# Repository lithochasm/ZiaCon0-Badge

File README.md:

# ZiaCon0-Badge
Badge code and hardware schematics for the ZiaCon0 Badge

KiCad project and gerbers are located in the Hardware Folder

An Ardunio project is located in the software folder. Please note that
the .ino project is blank. It just pulls in the tinytouch libraries. In the 
tinytouch library folder there is a main.c file which contains the badge code.
I did not have time to pull the code out of there and make a proper ardunio project so
I just ran with what the library was already pointing to. 

# Resources

How to program an ATTiny13A with an arduino: https://www.hackster.io/taunoerik/programming-attiny13-with-arduino-uno-07beba

Low Power tips for an ATTiny13: https://homecircuits.eu/blog/low-power-picopower-attiny13a/

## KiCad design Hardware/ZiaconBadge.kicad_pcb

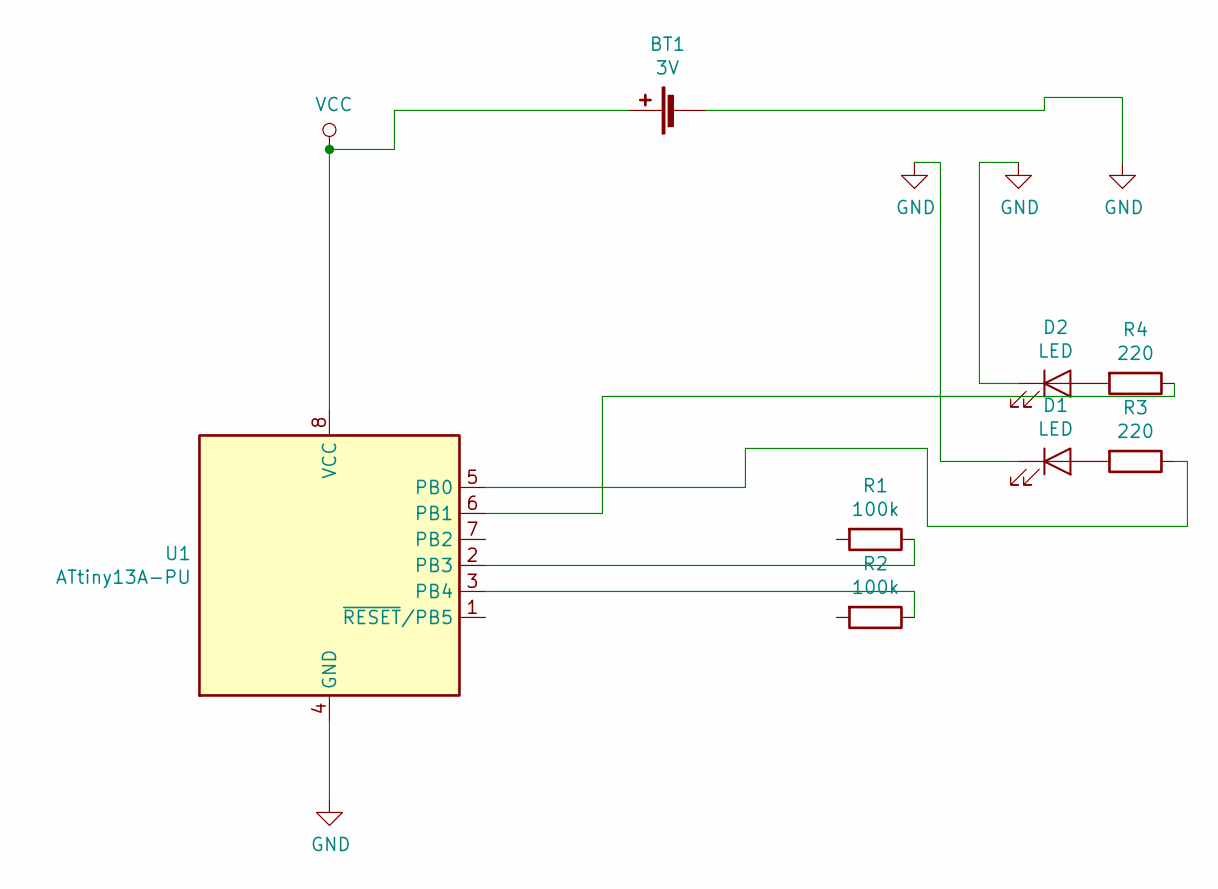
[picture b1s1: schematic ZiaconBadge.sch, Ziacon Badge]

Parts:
BT1: 3V; Battery_Holder_Coin_2032_BS-7
D1, D2: LED; LED_D3.0mm
R1, R2: 100k; R_Axial_DIN0207_L6.3mm_D2.5mm_P7.62mm_Horizontal
R3, R4: 220; R_Axial_DIN0207_L6.3mm_D2.5mm_P7.62mm_Horizontal
U1: ATtiny13A-PU; DIP-8_W7.62mm

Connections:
GND: BT1.2 (-), D1.1 (K), D2.1 (K), U1.4 (GND)
unnamed: D1.2 (A), R3.2
unnamed: D2.2 (A), R4.2
unnamed: R1.1, U1.2 (PB3)
unnamed: R2.1, U1.3 (PB4)
unnamed: R3.1, U1.5 (PB0)
unnamed: R4.1, U1.6 (PB1)
VCC: BT1.1 (+), U1.8 (VCC)

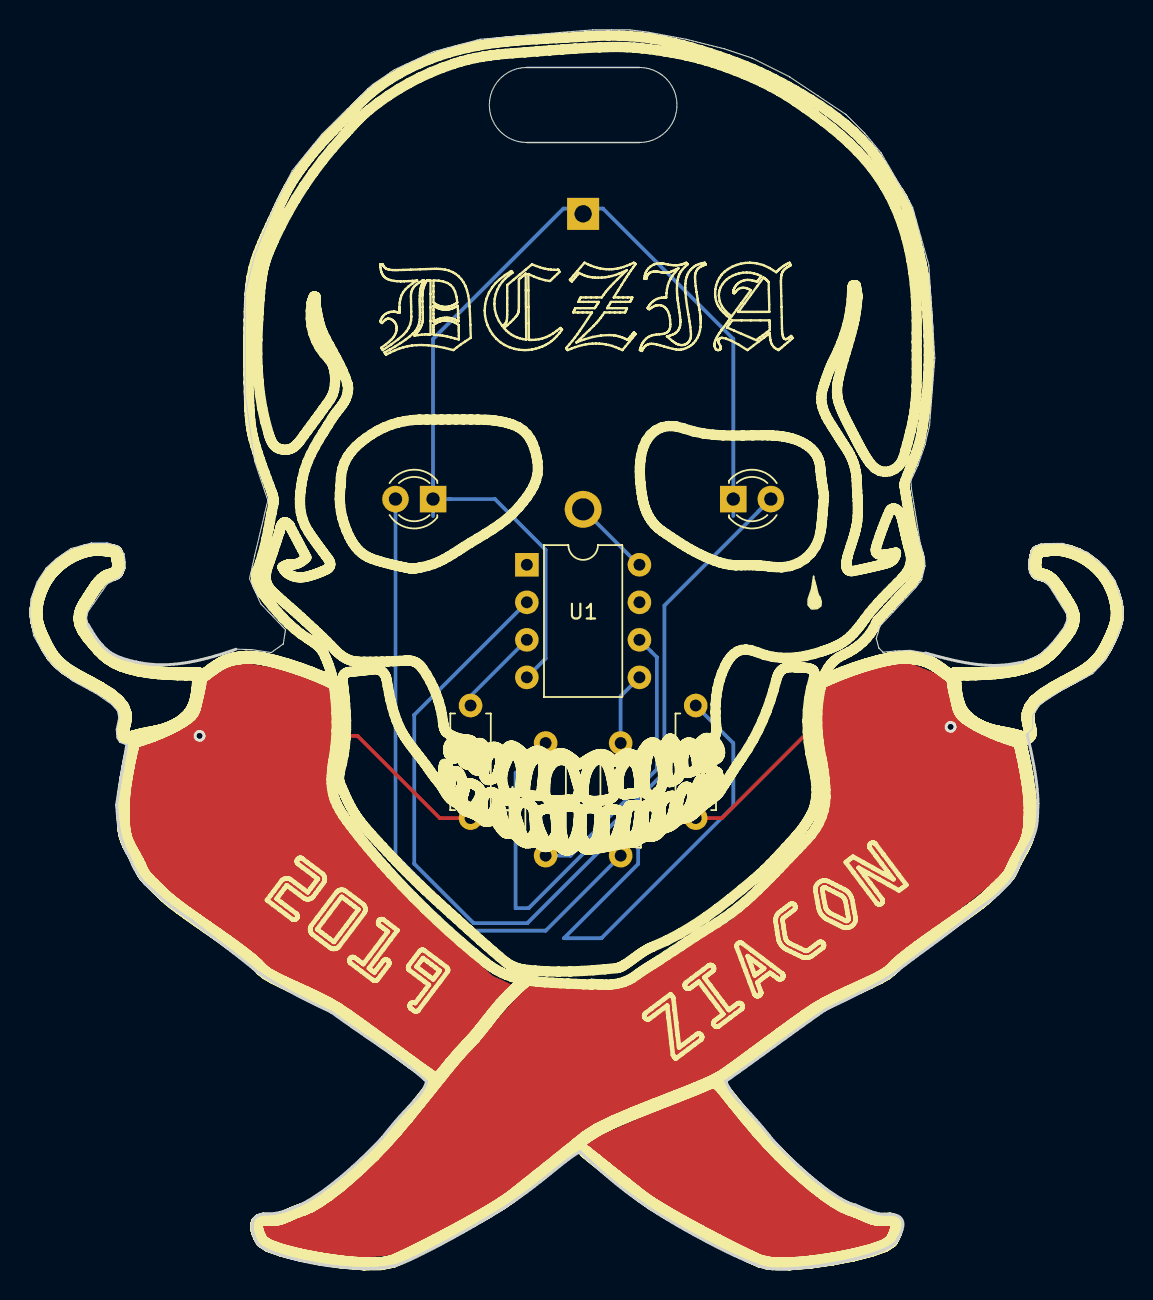
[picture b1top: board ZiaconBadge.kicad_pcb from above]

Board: 2 copper layers, 73.8 x 83.8 mm, 8 parts (1 on the bottom side), 8 nets.

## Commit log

2019-05-08 Added images, cleaned up hardware, added presentation
2019-05-13 Added Code for ATTiny13A
2019-05-18 Update README.md
    Added link on howto program an ATTiny13A
